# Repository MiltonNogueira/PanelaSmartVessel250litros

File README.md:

# PanelaSmartVessel250litros
 Controlador panela cervejeira single vessel

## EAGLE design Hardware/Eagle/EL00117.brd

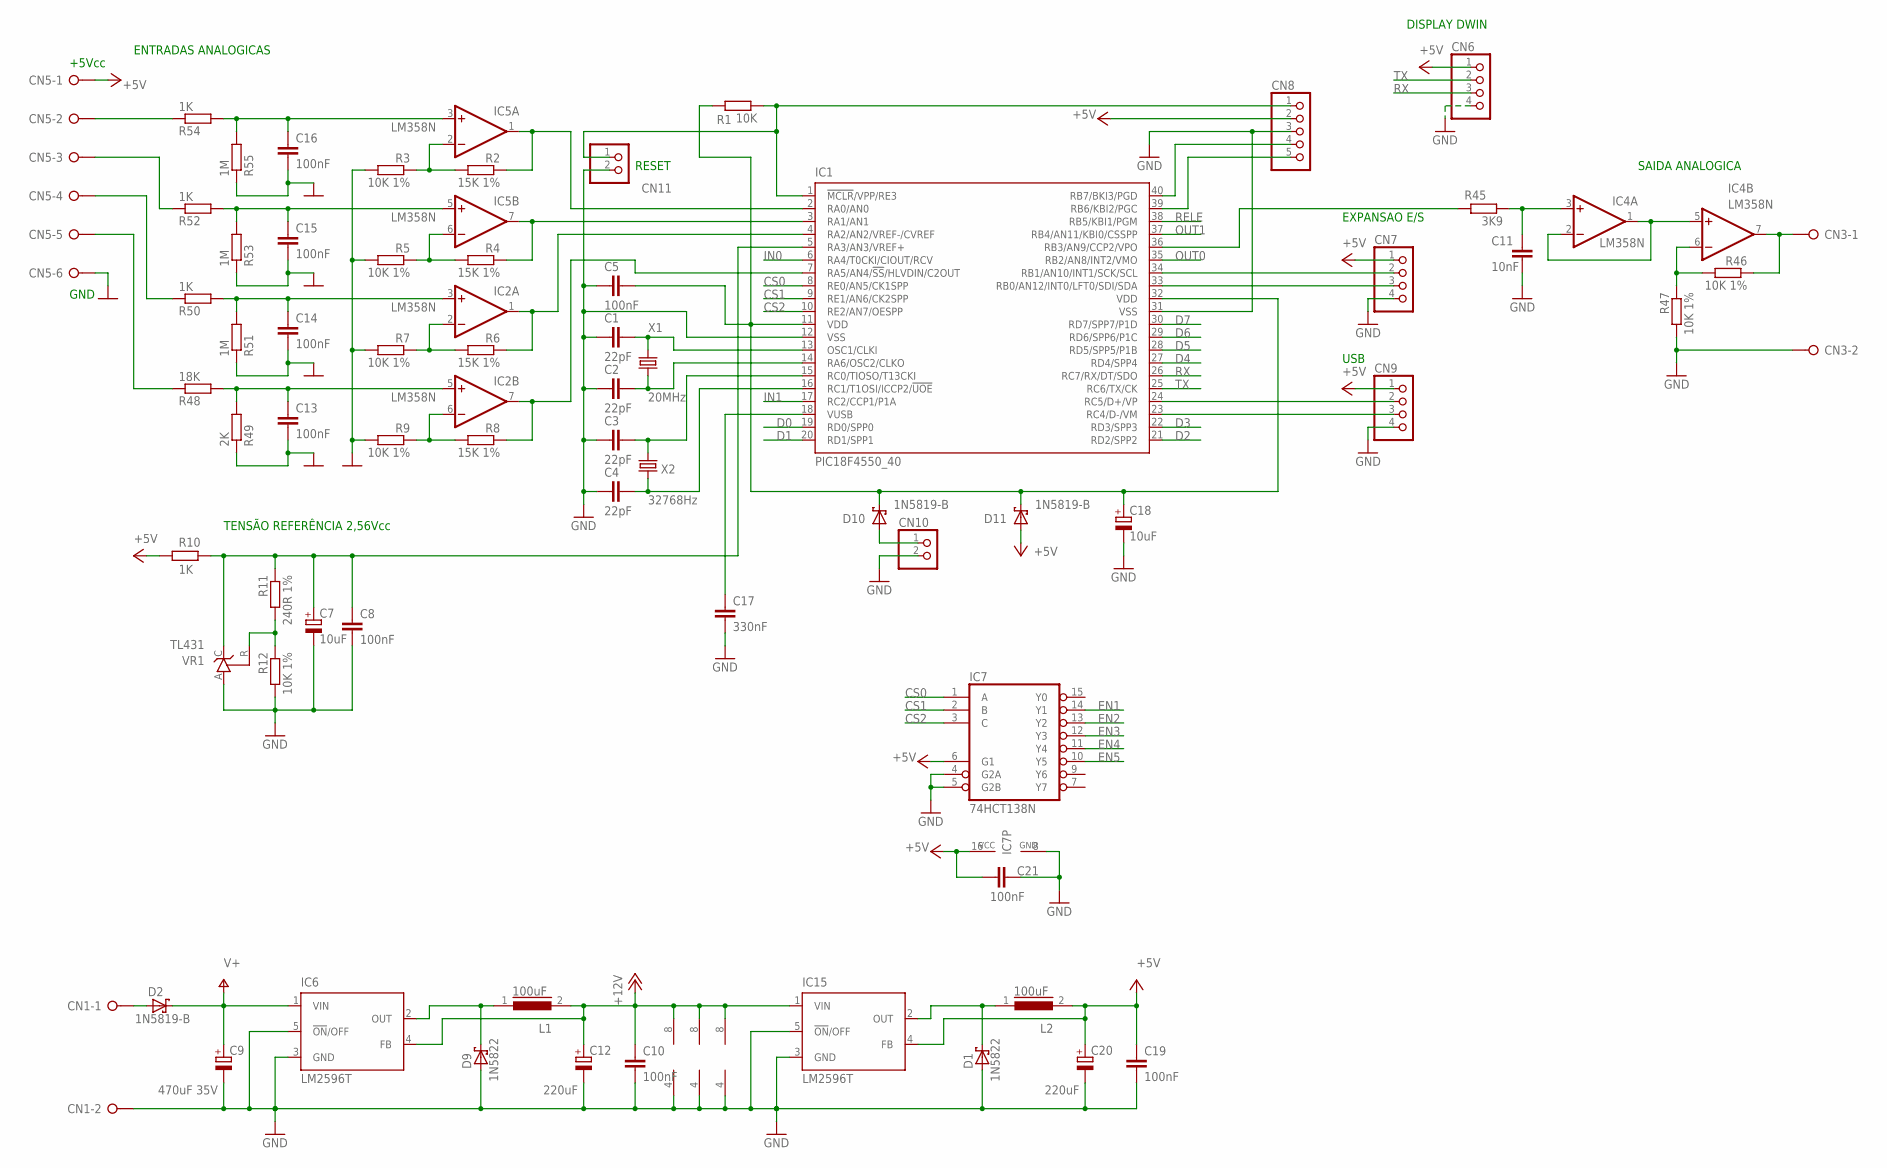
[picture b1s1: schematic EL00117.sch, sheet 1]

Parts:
C1, C2, C3, C4: 22pF; C050-024X044
C5, C8, C10, C13, C14, C15, C16, C19, C21: 100nF; C050-024X044
C7, C18: 10uF; E2,5-6
C9: 470uF 35V; E3,5-10
C11: 10nF; C050-024X044
C12, C20: 220uF; E2,5-5
C17: 330nF; C050-024X044
CN1, CN3: W237-02P; W237-132
CN5: W237-06P; W237-6P
CN6, CN7, CN9: PINHD-1X4; 1X04
CN8: PINHD-1X5; 1X05
CN10, CN11: PINHD-1X2; 1X02
D1, D9: 1N5822; DO41-7.6
D2, D10, D11: 1N5819-B; DO41-7.6
IC1: PIC18F4550_40; DIL40
IC2, IC4, IC5: LM358N; DIL08
IC6, IC15: LM2596T; T05D
IC7: 74HCT138N; DIL16
L1, L2: 100uF; 82114R
R1: 10K; 0309V
R2, R4, R6, R8: 15K 1%; 0309V
R3, R5, R7, R9, R12, R46, R47: 10K 1%; 0309V
R10, R50, R52, R54: 1K; 0309V
R11: 240R 1%; 0309V
R45: 3K9; 0309V
R48: 18K; 0309V
R49: 2K; 0309V
R51, R53, R55: 1M; 0309V
VR1: TL431; TO92-CLP
X1: 20MHz; HC49U-V
X2: 32768Hz; TC26V

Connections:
+5V: C19.2, C20.+, C21.2, CN5.1, CN6.1, CN7.1, CN8.2, CN9.1, D11.A, IC7.6 (G1), IC7.16 (VCC), IC15.4 (FB), L2.2, R10.2; also elsewhere on the board
+12V: C10.2, C12.+, IC2.8 (V+), IC4.8 (V+), IC5.8 (V+), IC6.4 (FB), IC15.1 (VIN), L1.2; also elsewhere on the board
CS0: IC1.8 (RE0/AN5/CK1SPP), IC7.1 (A)
CS1: IC1.9 (RE1/AN6/CK2SPP), IC7.2 (B)
CS2: IC1.10 (RE2/AN7/OESPP), IC7.3 (C)
D0: IC1.19 (RD0/SPP0); also elsewhere on the board
D1: IC1.20 (RD1/SPP1); also elsewhere on the board
D2: IC1.21 (RD2/SPP2); also elsewhere on the board
D3: IC1.22 (RD3/SPP3); also elsewhere on the board
D4: IC1.27 (RD4/SPP4); also elsewhere on the board
D5: IC1.28 (RD5/SPP5/P1B); also elsewhere on the board
D6: IC1.29 (RD6/SPP6/P1C); also elsewhere on the board
D7: IC1.30 (RD7/SPP7/P1D); also elsewhere on the board
EN1: IC7.14 (Y1); also elsewhere on the board
EN2: IC7.13 (Y2); also elsewhere on the board
EN3: IC7.12 (Y3); also elsewhere on the board
EN4: IC7.11 (Y4); also elsewhere on the board
EN5: IC7.10 (Y5); also elsewhere on the board
GND: C1.1, C2.1, C3.1, C4.1, C5.1, C7.-, C8.1, C9.-, C10.1, C11.1, C12.-, C13.1, C14.1, C15.1, C16.1, C17.1, C18.-, C19.1, C20.-, C21.1, CN1.2, CN3.2, CN5.6, CN6.4, CN7.4, CN8.3, CN9.4, CN10.2, CN11.2, D1.A, D9.A, IC1.12 (VSS), IC1.31 (VSS), IC2.4 (V-), IC4.4 (V-), IC5.4 (V-), IC6.3 (GND), IC6.5 (!ON!/OFF), IC7.4 (G2A), IC7.5 (G2B), IC7.8 (GND), IC15.3 (GND), IC15.5 (!ON!/OFF), R3.2, R5.2, R7.2, R9.2, R12.2, R47.2, R49.1, R51.1, R53.1, R55.1, VR1.A; also elsewhere on the board
IN0: IC1.6 (RA4/T0CKI/CIOUT/RCV); also elsewhere on the board
IN1: IC1.17 (RC2/CCP1/P1A); also elsewhere on the board
unnamed: C1.2, IC1.13 (OSC1/CLKI), X1.2
unnamed: C2.2, IC1.14 (RA6/OSC2/CLKO), X1.1
unnamed: C3.2, IC1.15 (RC0/TIOSO/T13CKI), X2.2
unnamed: C4.2, IC1.16 (RC1/T1OSI/ICCP2/!UOE), X2.1
unnamed: CN8.1, CN11.1, IC1.1 (!MCLR!/VPP/RE3), R1.1
unnamed: IC5.2 (-IN), R2.2, R3.1
unnamed: IC1.2 (RA0/AN0), IC5.1 (OUT), R2.1
unnamed: IC1.3 (RA1/AN1), IC5.7 (OUT), R4.1
unnamed: IC5.6 (-IN), R4.2, R5.1
unnamed: CN5.2, R54.1
unnamed: IC2.2 (-IN), R6.2, R7.1
unnamed: IC2.6 (-IN), R8.2, R9.1
unnamed: IC1.7 (RA5/AN4/!SS!/HLVDIN/C2OUT), IC2.7 (OUT), R8.1
unnamed: CN5.3, R52.1
unnamed: CN5.4, R50.1
unnamed: CN5.5, R48.1
unnamed: C7.+, C8.2, IC1.5 (RA3/AN3/VREF+), R10.1, R11.1, VR1.C
unnamed: R11.2, R12.1, VR1.R
unnamed: IC1.4 (RA2/AN2/VREF-/CVREF), IC2.1 (OUT), R6.1
unnamed: CN1.1, D2.A
unnamed: C13.2, IC2.5 (+IN), R48.2, R49.2
unnamed: C15.2, IC5.5 (+IN), R52.2, R53.2
unnamed: CN7.2, IC1.34 (RB1/AN10/INT1/SCK/SCL)
unnamed: CN7.3, IC1.33 (RB0/AN12/INT0/LFT0/SDI/SDA)
unnamed: IC4.1 (OUT), IC4.2 (-IN), IC4.5 (+IN)
unnamed: C11.2, IC4.3 (+IN), R45.1
unnamed: IC1.36 (RB3/AN9/CCP2/VPO), R45.2
unnamed: IC4.6 (-IN), R46.2, R47.1
unnamed: CN3.1, IC4.7 (OUT), R46.1
unnamed: CN9.2, IC1.24 (RC5/D+/VP)
unnamed: CN9.3, IC1.23 (RC4/D-/VM)
unnamed: C5.2, C18.+, D10.C, D11.C, IC1.11 (VDD), IC1.32 (VDD), R1.2
unnamed: C17.2, IC1.18 (VUSB)
unnamed: CN8.4, IC1.40 (RB7/BKI3/PGD)
unnamed: CN8.5, IC1.39 (RB6/KBI2/PGC)
unnamed: CN10.1, D10.A
unnamed: D9.C, IC6.2 (OUT), L1.1
unnamed: C16.2, IC5.3 (+IN), R54.2, R55.2
unnamed: C14.2, IC2.3 (+IN), R50.2, R51.2
unnamed: D1.C, IC15.2 (OUT), L2.1
OUT0: IC1.35 (RB2/AN8/INT2/VMO); also elsewhere on the board
OUT1: IC1.37 (RB4/AN11/KBI0/CSSPP); also elsewhere on the board
RELE: IC1.38 (RB5/KBI1/PGM); also elsewhere on the board
RX: CN6.3, IC1.26 (RC7/RX/DT/SDO)
TX: CN6.2, IC1.25 (RC6/TX/CK)
V+: C9.+, D2.C, IC6.1 (VIN)

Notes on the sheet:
RESET
+5Vcc
GND
ENTRADAS ANALOGICAS
TENSÃO REFERÊNCIA 2,56Vcc
DISPLAY DWIN
EXPANSAO E/S
SAIDA ANALOGICA
USB

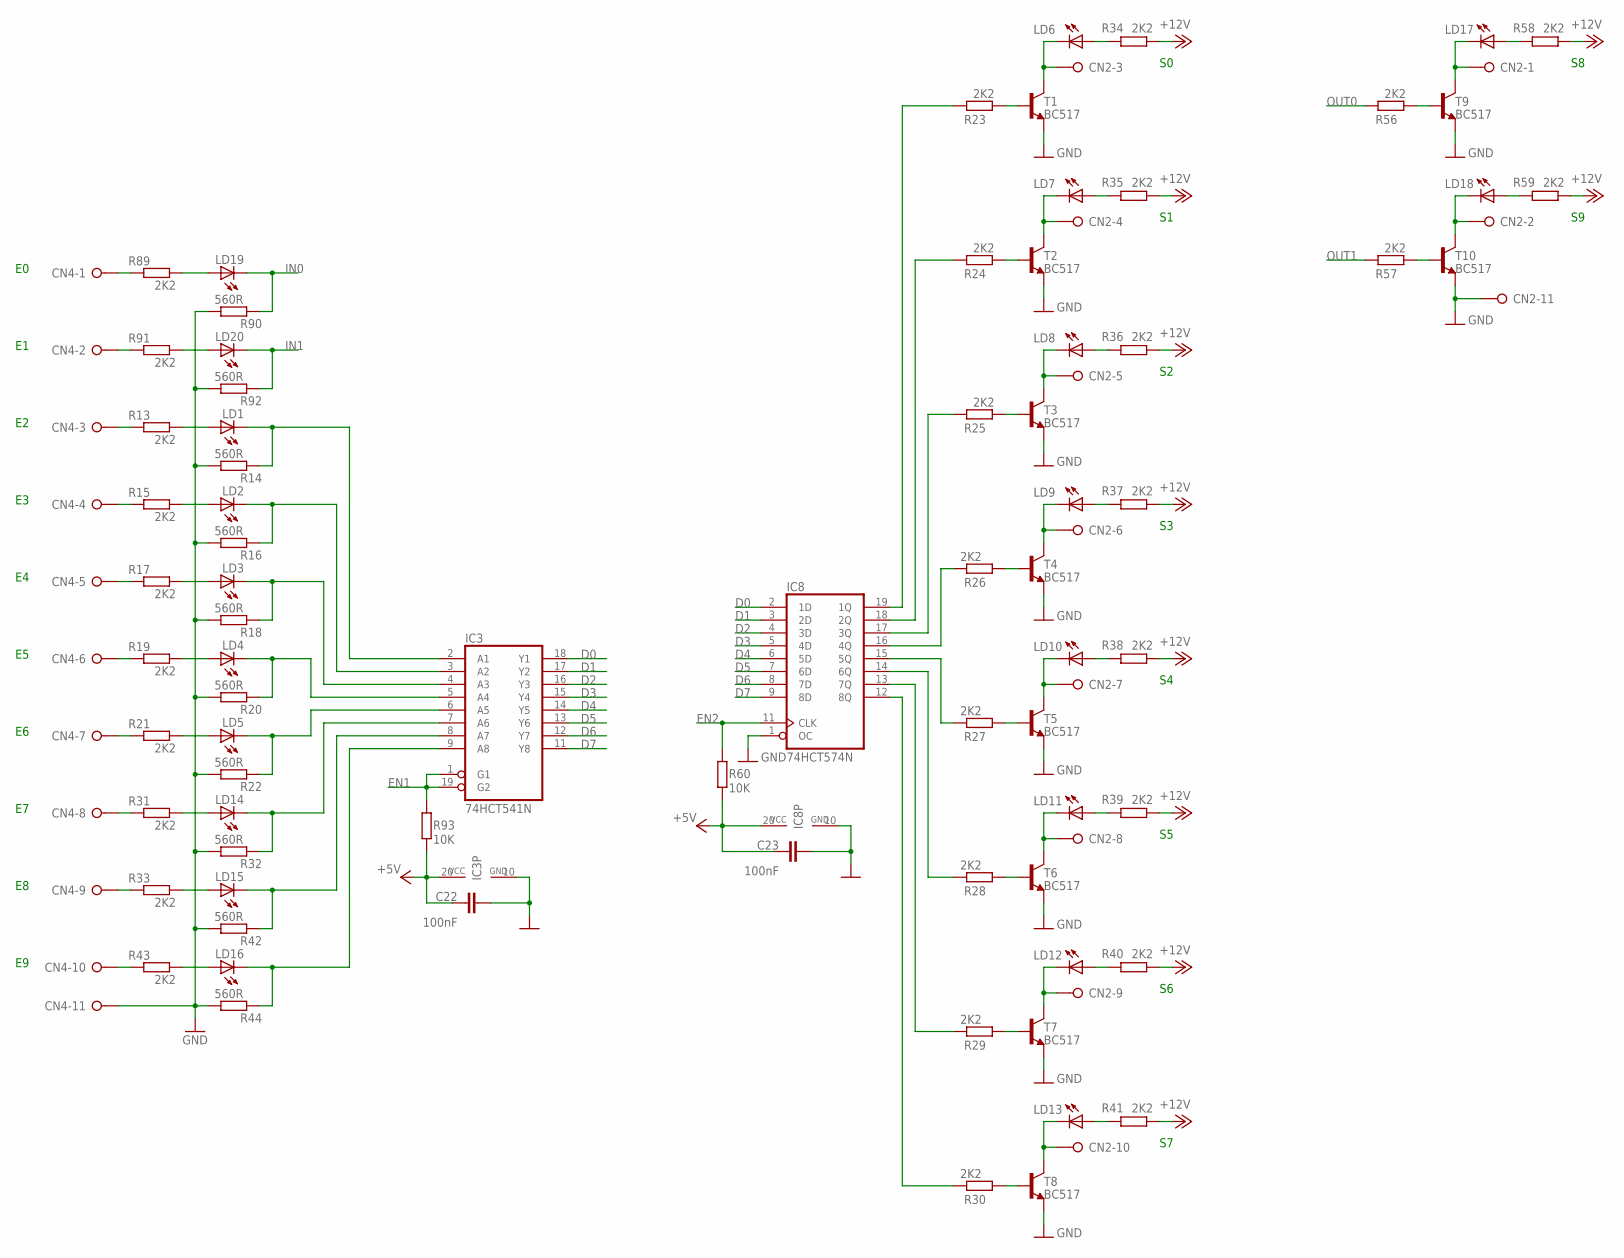
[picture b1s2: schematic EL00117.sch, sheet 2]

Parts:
C22, C23: 100nF; C050-024X044
CN2, CN4: W237-11P
IC3: 74HCT541N; DIL20
IC8: 74HCT574N; DIL20
LD1, LD2, LD3, LD4, LD5, LD6, LD7, LD8, LD9, LD10, LD11, LD12, LD13, LD14, LD15, LD16, LD17, LD18, LD19, LD20: LED3MM
R13, R15, R17, R19, R21, R23, R24, R25, R26, R27, R28, R29, R30, R31, R33, R34, R35, R36, R37, R38, R39, R40, R41, R43, R56, R57, R58, R59, R89, R91: 2K2; 0309V
R14, R16, R18, R20, R22, R32, R42, R44, R90, R92: 560R; 0309V
R60, R93: 10K; 0309V
T1, T2, T3, T4, T5, T6, T7, T8, T9, T10: BC517; TO92-CBE

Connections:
+5V: C22.1, C23.1, IC3.20 (VCC), IC8.20 (VCC), R60.2, R93.2; also elsewhere on the board
+12V: R34.1, R35.1, R36.1, R37.1, R38.1, R39.1, R40.1, R41.1, R58.1, R59.1; also elsewhere on the board
D0: IC3.18 (Y1), IC8.2 (1D); also elsewhere on the board
D1: IC3.17 (Y2), IC8.3 (2D); also elsewhere on the board
D2: IC3.16 (Y3), IC8.4 (3D); also elsewhere on the board
D3: IC3.15 (Y4), IC8.5 (4D); also elsewhere on the board
D4: IC3.14 (Y5), IC8.6 (5D); also elsewhere on the board
D5: IC3.13 (Y6), IC8.7 (6D); also elsewhere on the board
D6: IC3.12 (Y7), IC8.8 (7D); also elsewhere on the board
D7: IC3.11 (Y8), IC8.9 (8D); also elsewhere on the board
ED0: IC3.2 (A1), LD1.K (C), R14.2
ED1: IC3.3 (A2), LD2.K (C), R16.2
ED2: IC3.4 (A3), LD3.K (C), R18.2
ED3: IC3.5 (A4), LD4.K (C), R20.2
ED4: IC3.6 (A5), LD5.K (C), R22.2
ED5: IC3.7 (A6), LD14.K (C), R32.2
ED6: IC3.8 (A7), LD15.K (C), R42.2
ED7: IC3.9 (A8), LD16.K (C), R44.2
EN1: IC3.1 (G1), IC3.19 (G2), R93.1; also elsewhere on the board
EN2: IC8.11 (CLK), R60.1; also elsewhere on the board
GND: C22.2, C23.2, CN2.11, CN4.11, IC3.10 (GND), IC8.1 (OC), IC8.10 (GND), R14.1, R16.1, R18.1, R20.1, R22.1, R32.1, R42.1, R44.1, R90.1, R92.1, T1.E, T2.E, T3.E, T4.E, T5.E, T6.E, T7.E, T8.E, T9.E, T10.E; also elsewhere on the board
IN0: LD19.K (C), R90.2; also elsewhere on the board
IN1: LD20.K (C), R92.2; also elsewhere on the board
unnamed: R56.2, T9.B
unnamed: R57.2, T10.B
unnamed: R29.2, T7.B
unnamed: LD1.A, R13.1
unnamed: R30.2, T8.B
unnamed: CN2.1, LD17.K (C), T9.C
unnamed: LD2.A, R15.1
unnamed: R23.2, T1.B
unnamed: LD3.A, R17.1
unnamed: R24.2, T2.B
unnamed: LD4.A, R19.1
unnamed: LD5.A, R21.1
unnamed: R25.2, T3.B
unnamed: CN4.1, R89.2
unnamed: R26.2, T4.B
unnamed: R27.2, T5.B
unnamed: R28.2, T6.B
unnamed: CN4.2, R91.2
unnamed: CN4.3, R13.2
unnamed: CN4.4, R15.2
unnamed: CN4.5, R17.2
unnamed: CN2.3, LD6.K (C), T1.C
unnamed: CN2.4, LD7.K (C), T2.C
unnamed: LD6.A, R34.2
unnamed: LD7.A, R35.2
unnamed: CN2.5, LD8.K (C), T3.C
unnamed: LD8.A, R36.2
unnamed: CN2.6, LD9.K (C), T4.C
unnamed: LD9.A, R37.2
unnamed: CN2.7, LD10.K (C), T5.C
unnamed: CN2.8, LD11.K (C), T6.C
unnamed: LD10.A, R38.2
unnamed: LD11.A, R39.2
unnamed: CN2.9, LD12.K (C), T7.C
unnamed: LD12.A, R40.2
unnamed: CN2.10, LD13.K (C), T8.C
unnamed: LD13.A, R41.2
unnamed: CN2.2, LD18.K (C), T10.C
unnamed: LD17.A, R58.2
unnamed: LD18.A, R59.2
unnamed: LD14.A, R31.1
unnamed: CN4.6, R19.2
unnamed: CN4.7, R21.2
unnamed: CN4.8, R31.2
unnamed: LD15.A, R33.1
unnamed: CN4.9, R33.2
unnamed: CN4.10, R43.2
unnamed: LD16.A, R43.1
unnamed: IC8.16 (4Q), R26.1
unnamed: IC8.15 (5Q), R27.1
unnamed: IC8.17 (3Q), R25.1
unnamed: IC8.18 (2Q), R24.1
unnamed: IC8.19 (1Q), R23.1
unnamed: IC8.14 (6Q), R28.1
unnamed: IC8.13 (7Q), R29.1
unnamed: IC8.12 (8Q), R30.1
unnamed: LD19.A, R89.1
unnamed: LD20.A, R91.1
OUT0: R56.1; also elsewhere on the board
OUT1: R57.1; also elsewhere on the board

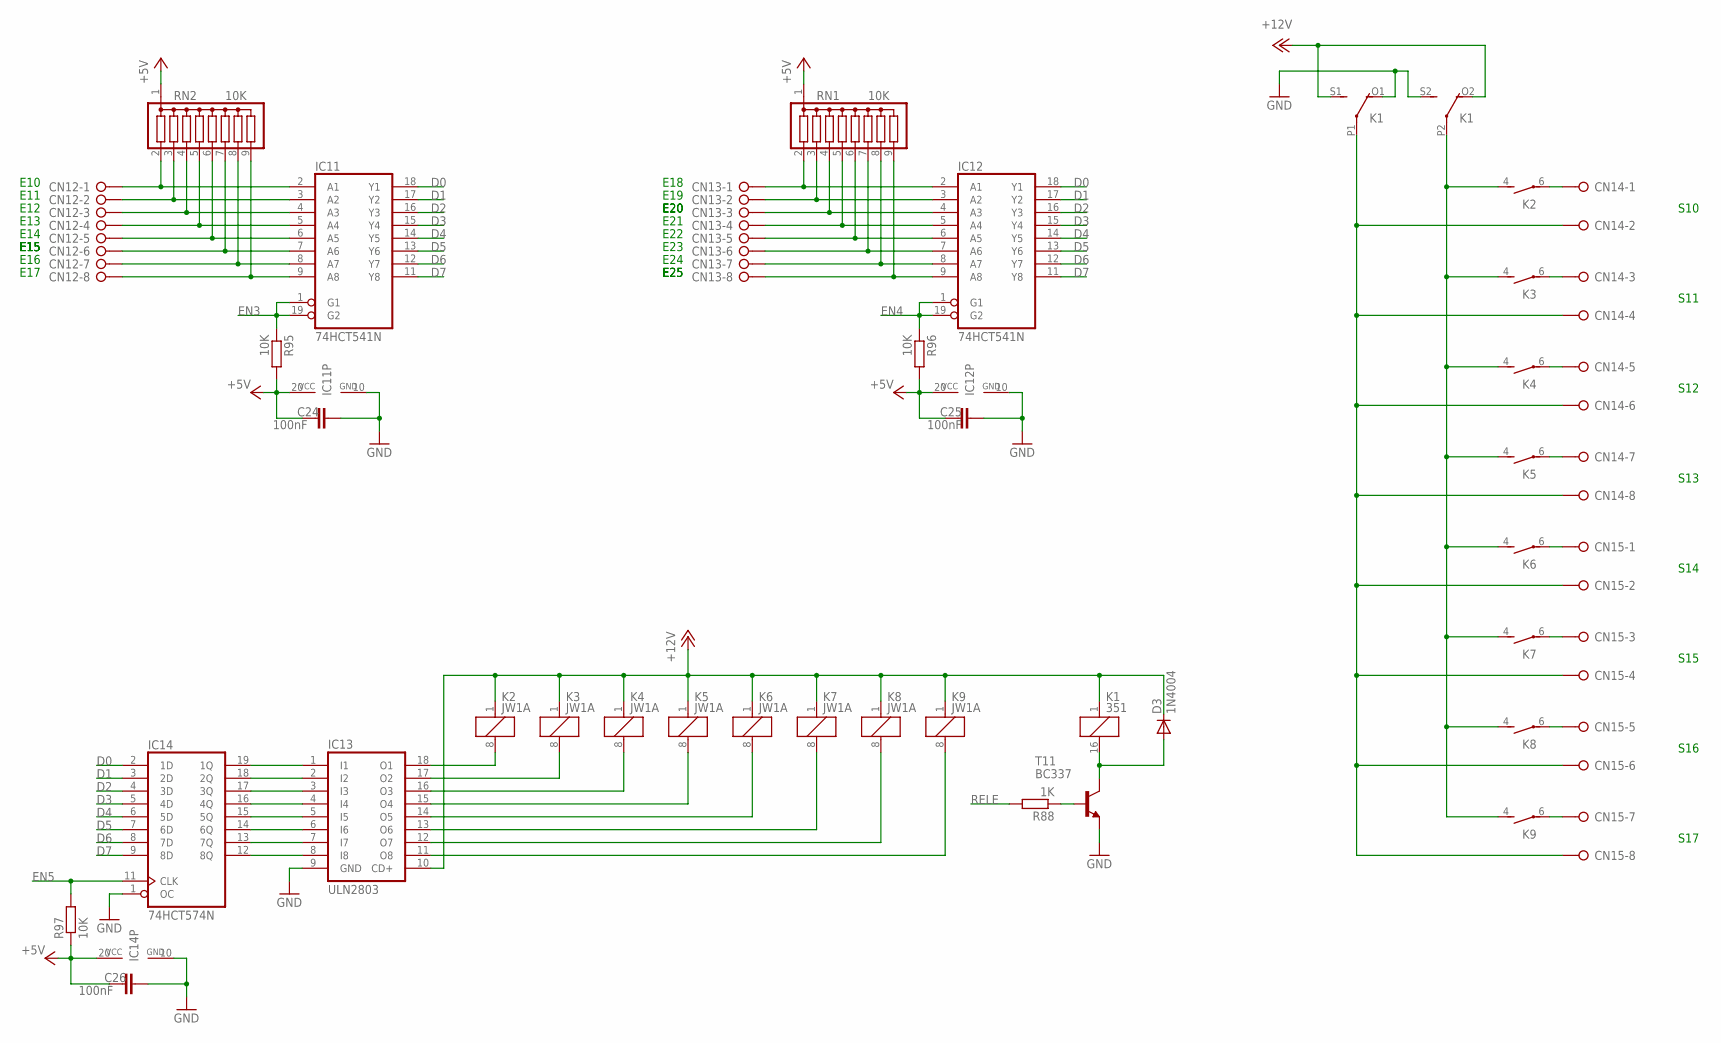
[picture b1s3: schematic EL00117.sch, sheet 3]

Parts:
C24, C25, C26: 100nF; C050-024X044
CN12, CN13, CN14, CN15: W237-08P; W237-8P
D3: 1N4004; DO41-10
IC11, IC12: 74HCT541N; DIL20
IC13: ULN2803; DIL18
IC14: 74HCT574N; DIL20
K1: 351
K2, K3, K4, K5, K6, K7, K8, K9: JW1A
R88: 1K; 0309V
R95, R96, R97: 10K; 0309V
RN1, RN2: 10K; SIL9
T11: BC337; TO92

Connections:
+5V: C24.1, C25.2, C26.2, IC11.20 (VCC), IC12.20 (VCC), IC14.20 (VCC), R95.2, R96.2, R97.1, RN1.1, RN2.1; also elsewhere on the board
+12V: D3.C, IC13.10 (CD+), K1.1, K1.O2 (O), K1.S1 (S), K2.1, K3.1, K4.1, K5.1, K6.1, K7.1, K8.1, K9.1; also elsewhere on the board
D0: IC11.18 (Y1), IC12.18 (Y1), IC14.2 (1D); also elsewhere on the board
D1: IC11.17 (Y2), IC12.17 (Y2), IC14.3 (2D); also elsewhere on the board
D2: IC11.16 (Y3), IC12.16 (Y3), IC14.4 (3D); also elsewhere on the board
D3: IC11.15 (Y4), IC12.15 (Y4), IC14.5 (4D); also elsewhere on the board
D4: IC11.14 (Y5), IC12.14 (Y5), IC14.6 (5D); also elsewhere on the board
D5: IC11.13 (Y6), IC12.13 (Y6), IC14.7 (6D); also elsewhere on the board
D6: IC11.12 (Y7), IC12.12 (Y7), IC14.8 (7D); also elsewhere on the board
D7: IC11.11 (Y8), IC12.11 (Y8), IC14.9 (8D); also elsewhere on the board
EN3: IC11.1 (G1), IC11.19 (G2), R95.1; also elsewhere on the board
EN4: IC12.1 (G1), IC12.19 (G2), R96.1; also elsewhere on the board
EN5: IC14.11 (CLK), R97.2; also elsewhere on the board
GND: C24.2, C25.1, C26.1, IC11.10 (GND), IC12.10 (GND), IC13.9 (GND), IC14.1 (OC), IC14.10 (GND), K1.O1 (O), K1.S2 (S), T11.1 (E); also elsewhere on the board
unnamed: CN12.1, IC11.2 (A1), RN2.2
unnamed: IC13.18 (O1), K2.8 (2)
unnamed: CN12.2, IC11.3 (A2), RN2.3
unnamed: CN12.3, IC11.4 (A3), RN2.4
unnamed: CN12.4, IC11.5 (A4), RN2.5
unnamed: CN12.5, IC11.6 (A5), RN2.6
unnamed: CN12.6, IC11.7 (A6), RN2.7
unnamed: CN12.7, IC11.8 (A7), RN2.8
unnamed: CN12.8, IC11.9 (A8), RN2.9
unnamed: CN13.1, IC12.2 (A1), RN1.2
unnamed: CN13.2, IC12.3 (A2), RN1.3
unnamed: CN13.3, IC12.4 (A3), RN1.4
unnamed: CN13.4, IC12.5 (A4), RN1.5
unnamed: CN13.5, IC12.6 (A5), RN1.6
unnamed: CN13.6, IC12.7 (A6), RN1.7
unnamed: CN13.7, IC12.8 (A7), RN1.8
unnamed: CN13.8, IC12.9 (A8), RN1.9
unnamed: K1.P2, K2.4 (S), K3.4 (S), K4.4 (S), K5.4 (S), K6.4 (S), K7.4 (S), K8.4 (S), K9.4 (S)
unnamed: IC13.17 (O2), K3.8 (2)
unnamed: CN14.1, K2.6
unnamed: CN14.3, K3.6
unnamed: CN14.5, K4.6
unnamed: CN14.7, K5.6
unnamed: CN15.1, K6.6
unnamed: CN15.3, K7.6
unnamed: CN15.5, K8.6
unnamed: CN15.7, K9.6
unnamed: IC13.16 (O3), K4.8 (2)
unnamed: IC13.15 (O4), K5.8 (2)
unnamed: IC13.14 (O5), K6.8 (2)
unnamed: IC13.13 (O6), K7.8 (2)
unnamed: IC13.12 (O7), K8.8 (2)
unnamed: IC13.11 (O8), K9.8 (2)
unnamed: R88.1, T11.2 (B)
unnamed: IC13.1 (I1), IC14.19 (1Q)
unnamed: CN14.2, CN14.4, CN14.6, CN14.8, CN15.2, CN15.4, CN15.6, CN15.8, K1.P1
unnamed: IC13.2 (I2), IC14.18 (2Q)
unnamed: IC13.3 (I3), IC14.17 (3Q)
unnamed: IC13.4 (I4), IC14.16 (4Q)
unnamed: IC13.5 (I5), IC14.15 (5Q)
unnamed: IC13.6 (I6), IC14.14 (6Q)
unnamed: IC13.7 (I7), IC14.13 (7Q)
unnamed: IC13.8 (I8), IC14.12 (8Q)
unnamed: D3.A, K1.16 (2), T11.3 (C)
RELE: R88.2; also elsewhere on the board

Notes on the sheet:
E10
E11
E12
E13
E14
E15
E16
E17
E18
E19
E20
E21
E22
E23
E24
E25
S10
S11
S12
S13
S14
S15
S16
S17

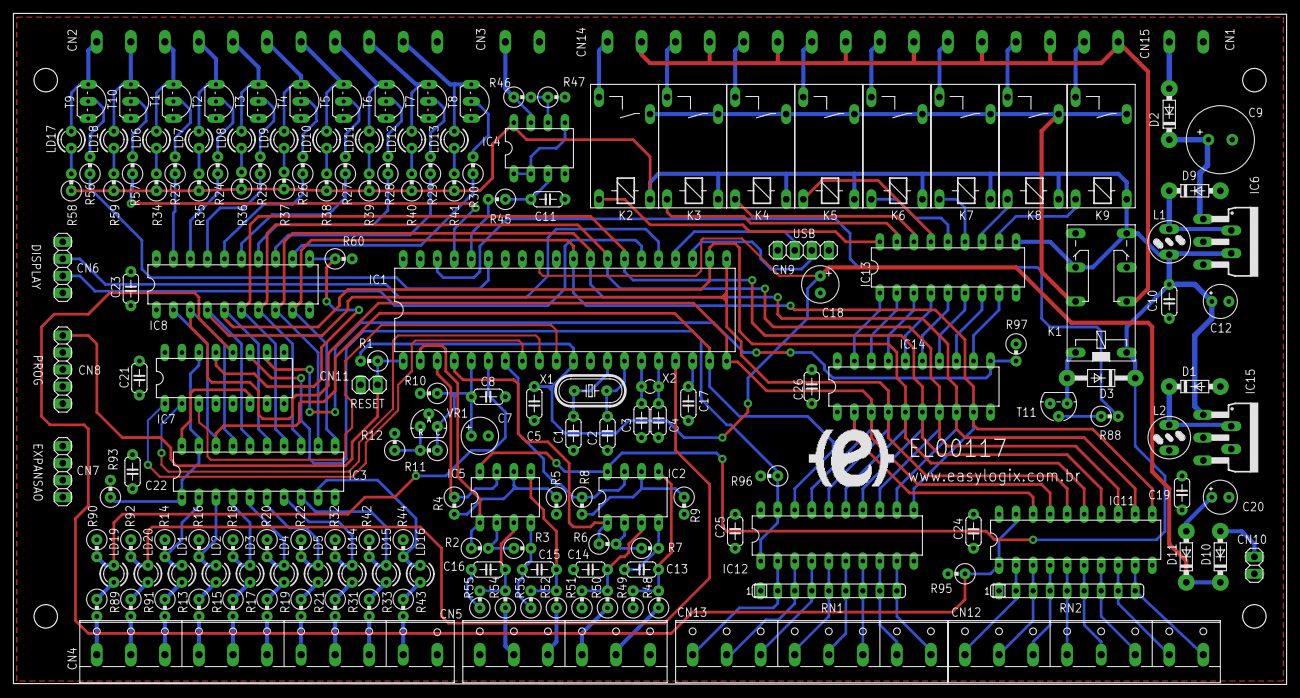
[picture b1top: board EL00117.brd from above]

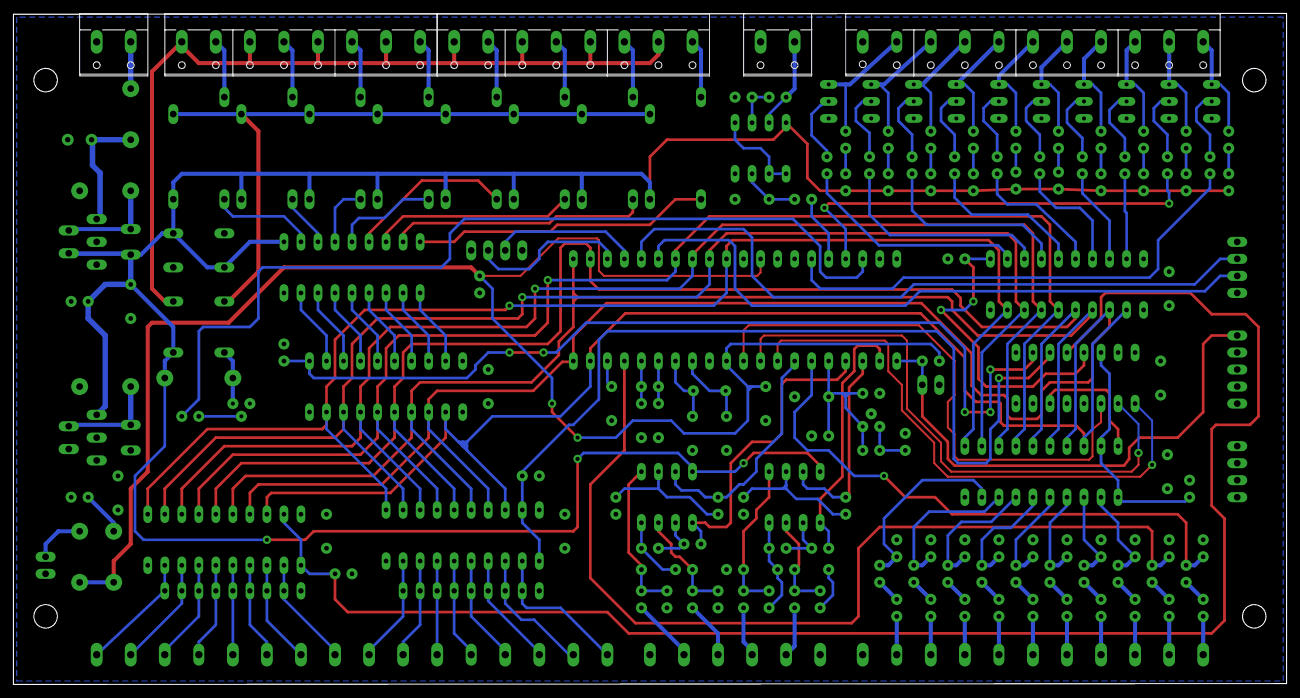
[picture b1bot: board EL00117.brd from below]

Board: 2 copper layers, 190.0 x 100.1 mm, 176 parts (5 on the bottom side), 177 nets.

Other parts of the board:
DRILEGEND: DRILEGEND

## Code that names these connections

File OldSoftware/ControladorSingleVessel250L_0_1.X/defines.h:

/*******************************************************************************
 * Definições do programa
 ******************************************************************************/
#define _XTAL_FREQ      20000000                // oscilador interno em valor default
#define FECHAR 0
#define ABRIR 1
#define PWMmin 1
#define PWMmax 199
#define CICLOSBOMBA 5
//Funcoes dos pinos do microcontrolador
#define SENTIDOVALVULA PORTBbits.RB5
#define VALVULAENTRADARESERVATORIO PORTDbits.RD0
#define VALVULASAIDARESERVATORIO PORTDbits.RD5
#define VALVULASAIDAPANELA PORTDbits.RD6
#define VALVULALAVAGEMGRAOS PORTDbits.RD7
#define VALVULAENTRADAPANELA PORTEbits.RE0
#define VALVULAWHIRLPOOL PORTEbits.RE1
#define VALVULAENTRADAMOSTOTROCADOR PORTEbits.RE2
#define VALVULAENTRADAAGUATROCADOR PORTDbits.RD1
#define RESISTENCIAPANELA PORTDbits.RD2
#define RESISTENCIARESERVATORIO PORTDbits.RD3
#define RELESSR PORTBbits.RB1
#define SIRENE PORTDbits.RD4
#define BOTAO_EMERGENCIA PORTAbits.RA4
#define BOTAO_START PORTCbits.RC2
#define NB_BOILER PORTBbits.RB2
#define NA_BOILER PORTBbits.RB4
//#define ED4 PORTBbits.RB5
#define TEMPERATURAPANELA
#define TEMPERATURARESERVATORIO
#define TEMPERATURASAIDATROCADOR
#define TEMPERATURAPANELA
#define MEDIA_AD 25
#define NUMBYTESRECEITA 38
#define KVOLUME 22
//#define TAMOSTRAGEMCONTROLEPI 30
//#define KP 4
//#define KI 4
#define LIMITEMINERRO -2        //limite erro temperatura
#define LIMITEMAXERRO 2         //ajustado para 0,5oC
#define LIMITEMAXSOMAERRO 50
#define LIMITEMINSOMAERRO -50
#define NUMTELAMENUPRINCIPAL 1
#define NUMTELABRASSAGEM 6
#define NUMTELARECEITA 4
#define NUMTELACONFIGURACAO 3
#define NUMTELAMANUAL 2

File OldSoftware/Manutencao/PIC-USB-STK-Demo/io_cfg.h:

/*********************************************************************
 *
 *                Microchip USB C18 Firmware Version 1.0
 *
 *********************************************************************
 * FileName:        io_cfg.h
 * Dependencies:    See INCLUDES section below
 * Processor:       PIC18
 * Compiler:        C18 2.30.01+
 * Company:         Microchip Technology, Inc.
 *
 * Software License Agreement
 *
 * The software supplied herewith by Microchip Technology Incorporated
 * (the Company) for its PICmicro® Microcontroller is intended and
 * supplied to you, the Companys customer, for use solely and
 * exclusively on Microchip PICmicro Microcontroller products. The
 * software is owned by the Company and/or its supplier, and is
 * protected under applicable copyright laws. All rights are reserved.
 * Any use in violation of the foregoing restrictions may subject the
 * user to criminal sanctions under applicable laws, as well as to
 * civil liability for the breach of the terms and conditions of this
 * license.
 *
 * THIS SOFTWARE IS PROVIDED IN AN AS IS CONDITION. NO WARRANTIES,
 * WHETHER EXPRESS, IMPLIED OR STATUTORY, INCLUDING, BUT NOT LIMITED
 * TO, IMPLIED WARRANTIES OF MERCHANTABILITY AND FITNESS FOR A
 * PARTICULAR PURPOSE APPLY TO THIS SOFTWARE. THE COMPANY SHALL NOT,
 * IN ANY CIRCUMSTANCES, BE LIABLE FOR SPECIAL, INCIDENTAL OR
 * CONSEQUENTIAL DAMAGES, FOR ANY REASON WHATSOEVER.
 *
 * Author               Date        Comment
 *~~~~~~~~~~~~~~~~~~~~~~~~~~~~~~~~~~~~~~~~~~~~~~~~~~~~~~~~~~~~~~~~~~~~
 * Rawin Rojvanit       11/19/04    Original.
 ********************************************************************/

#ifndef IO_CFG_H
#define IO_CFG_H

/** I N C L U D E S *************************************************/
#include "autofiles\usbcfg.h"

/** T R I S *********************************************************/
#define INPUT_PIN           1
#define OUTPUT_PIN          0

/** U S B ***********************************************************/
#define tris_usb_bus_sense  TRISAbits.TRISA1    // Input

#if defined(USE_USB_BUS_SENSE_IO)
#define usb_bus_sense       PORTAbits.RA1
#else
#define usb_bus_sense       1
#endif

#define tris_self_power     TRISAbits.TRISA2    // Input

#if defined(USE_SELF_POWER_SENSE_IO)
#define self_power          PORTAbits.RA2
#else
#define self_power          1
#endif

/** L E D ***********************************************************/
#define mInitAllLEDs()      LATD &= 0xF0; TRISD &= 0xF0;

#define mLED_1              LATDbits.LATD0
#define mLED_2              LATDbits.LATD1
#define mLED_3              LATDbits.LATD2
#define mLED_4              LATDbits.LATD3

#define mLED_1_On()         mLED_1 = 1;
#define mLED_2_On()         mLED_2 = 1;
#define mLED_3_On()         mLED_3 = 1;
#define mLED_4_On()         mLED_4 = 1;

#define mLED_1_Off()        mLED_1 = 0;
#define mLED_2_Off()        mLED_2 = 0;
#define mLED_3_Off()        mLED_3 = 0;
#define mLED_4_Off()        mLED_4 = 0;

#define mLED_1_Toggle()     mLED_1 = !mLED_1;
#define mLED_2_Toggle()     mLED_2 = !mLED_2;
#define mLED_3_Toggle()     mLED_3 = !mLED_3;
#define mLED_4_Toggle()     mLED_4 = !mLED_4;

/** S W I T C H *****************************************************/
#define mInitAllSwitches()  TRISBbits.TRISB4=1;TRISBbits.TRISB5=1;TRISBbits.TRISB6=1;TRISBbits.TRISB7=1;
#define mInitSwitch1()      TRISBbits.TRISB5=1;
#define mInitSwitch2()      TRISBbits.TRISB4=1;
#define mInitSwitch3()      TRISBbits.TRISB7=1;
#define mInitSwitch4()      TRISBbits.TRISB6=1;
#define sw1                 PORTBbits.RB5
#define sw2                 PORTBbits.RB4
#define sw3                 PORTBbits.RB7
#define sw4                 PORTBbits.RB6

/** P O T ***********************************************************/
#define mInitPOT()          TRISAbits.TRISA0=1;ADCON0=0x01;ADCON2=0x3C;

/** S P I : Chip Select Lines ***************************************/
#define tris_cs_temp_sensor TRISBbits.TRISB2    // Output
#define cs_temp_sensor      LATBbits.LATB2

#define tris_cs_sdmmc       TRISBbits.TRISB3    // Output
#define cs_sdmmc            LATBbits.LATB3

/** S D M M C *******************************************************/
#define TRIS_CARD_DETECT    TRISBbits.TRISB4    // Input
#define CARD_DETECT         PORTBbits.RB4

#define TRIS_WRITE_DETECT   TRISAbits.TRISA4    // Input
#define WRITE_DETECT        PORTAbits.RA4

#endif //IO_CFG_H
